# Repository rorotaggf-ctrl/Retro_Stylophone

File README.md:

# Retro Stylophone

A retro-style pocket synthesizer built with an ESP32 for **Hack Club Half-Life (Week 3: Design Your Instrument)**.

The instrument utilizes the ESP32's built-in capacitive touch peripheral to create a 13-pad chromatic keyboard directly out of exposed PCB copper pads, completely eliminating mechanical button wear and complex key soldering.

---

## Features

- **Microcontroller:** ESP32 NodeMCU (USB-C, dual-core 240 MHz, 320 KB SRAM)
- **Keyboard:** 13 capacitive touch PCB pads (Full chromatic octave: C4 to C5 including sharps/flats)
- **Sound Generation:** 5V Passive Piezo Buzzer driven via hardware PWM / DAC output
- **Modulation & Pitch-Bend:** 10K linear potentiometer for dynamic pitch modulation and glide effects
- **Octave / Mode Select:** SPDT mini slide switch for octave shifting and sound mode toggling
- **Form Factor:** Compact 2-layer PCB designed in KiCad with integrated GND planes

---

## Pinout Configuration

Everything is mounted using through-hole female pin headers so the ESP32 can be swapped or serviced at any time.

| Component | Pin Function | ESP32 Pin Header | Pin / GPIO | Notes |
| :--- | :--- | :--- | :--- | :--- |
| **Touch Keyboard** | C4 (Root) | `J2` Pin 13 | GPIO 4 | Capacitive Touch 0 |
| | C#4 | `J2` Pin 14 | GPIO 0 | Capacitive Touch 1 |
| | D4 | `J2` Pin 16 | GPIO 15 | Capacitive Touch 3 |
| | D#4 | `J2` Pin 15 | GPIO 2 | Capacitive Touch 2 |
| | E4 | `J1` Pin 15 | GPIO 13 | Capacitive Touch 4 |
| | F4 | `J1` Pin 13 | GPIO 12 | Capacitive Touch 5 |
| | F#4 | `J1` Pin 3 | GPIO 36 | High-impedance ADC antenna pad |
| | G4 | `J1` Pin 12 | GPIO 14 | Capacitive Touch 6 |
| | G#4 | `J1` Pin 4 | GPIO 39 | High-impedance ADC antenna pad |
| | A4 | `J1` Pin 11 | GPIO 27 | Capacitive Touch 7 |
| | A#4 | `J1` Pin 6 | GPIO 35 | High-impedance ADC antenna pad |
| | B4 (H4) | `J1` Pin 8 | GPIO 33 | Capacitive Touch 8 |
| | C5 (High C) | `J1` Pin 7 | GPIO 32 | Capacitive Touch 9 |
| **Audio Output** | Buzzer (+) | `J1` Pin 9 | GPIO 25 | Hardware PWM Audio Output |
| | Buzzer (-) | `J1` Pin 14 | GND | Common Ground |
| **Pitch Control** | Poti Wiper | `J1` Pin 5 | GPIO 34 | ADC1 Analog Input (0 - 3.3V) |
| | Poti Pin 1 / 3 | `J1` Pin 1 / 14 | 3V3 / GND | Potentiometer Reference Rails |
| **Octave Switch** | SW1 Center | `J2` Pin 8 | GPIO 19 | Active LOW (Internal Pull-Up) |
| | SW1 Pin 3 | `J1` Pin 14 | GND | Ground Reference Rail |

---

## Bill of Materials (BoM)

### Grant Funded Components (Tier 1 Limit: $30.00)

> [!NOTE]
> This parts list covers multipack items funded via Hack Club Half-Life. For the raw CSV file, see `BOM.csv`.

| Part | What it's for | Qty | Price (USD) | Price (EUR) | Vendor | Purchase Link |
| :--- | :--- | :--- | :--- | :--- | :--- | :--- |
| ESP32 NodeMCU USB-C (2-Pack) | Synthesizer sound engine & touch controller | 1 | $15.66 | 13,98 € | Amazon | [Amazon Link](https://www.amazon.de/dp/B0DB8CYQBS) |
| 10K Linear Potentiometer WH148 (10-Pack) | Pitch-bend and waveform modulation | 1 | $7.04 | 6,29 € | Amazon | [Amazon Link](https://www.amazon.de/dp/B0GVP99HZ2) |
| SPDT Mini Slide Switch (40-Pack) | Power and octave mode switch | 1 | $5.59 | 4,99 € | Amazon | [Amazon Link](https://www.amazon.de/dp/B07M9Z4CBP) |
| **Total** | | | **$28.29** | **25,26 €** | | |

*Remaining Tier 1 Budget: $1.71*

### Additional Self-Funded Components

> [!IMPORTANT]
> The following components are funded personally or sourced from existing workshop inventory to complete the build without exceeding the grant limit.

| Part | What it's for | Qty | Price (USD) | Price (EUR) | Vendor | Purchase Link |
| :--- | :--- | :--- | :--- | :--- | :--- | :--- |
| Custom 2-Layer PCB (5 copies) | Main stylophone PCB with capacitive touch pads | 1 | $8.10 | 7,23 € | JLCPCB | [JLCPCB Quote](https://jlcpcb.com/quote) |
| PCB Shipping (Standard Line) | Tracked delivery to Germany | 1 | $9.55 | 8,53 € | JLCPCB | [JLCPCB Quote](https://jlcpcb.com/quote) |
| Passive Piezo Buzzer 5V (20-Pack) | Acoustic square-wave chiptune audio output | 1 | $8.83 | 7,88 € | Amazon | [Amazon Link](https://www.amazon.de/dp/B0179I6LIK) |
| 100nF Ceramic Capacitors | Decoupling & noise filtering | 2 | $0.00 | 0,00 € | Inventory | Existing parts |
| Female Pin Headers 2.54mm | Removable socket for ESP32 | 2 | $0.00 | 0,00 € | Inventory | Existing parts |
| **Total Self-Funded** | | | **$26.48** | **23,64 €** | | |

---

## Software & Firmware

Developed in **VS Code** with PlatformIO and the Arduino framework.

- [ ] Hardware bench test (validating touch threshold tolerances, pot readings, and buzzer PWM)
- [ ] **Capacitive Touch Core:** Zero-bounce touch scanning for native touch pins (T0-T9) with adaptive baseline calibration
- [ ] **ADC Touch Matrix:** High-impedance antenna detection for remaining accidentals
- [ ] **Pitch-Bend & Glide:** Continuous frequency bend calculation via 10K potentiometer ADC readings
- [ ] **Octave Engine:** Real-time transposition (+12 semitones) via hardware slide switch
- [ ] **Chiptune Audio Driver:** Square-wave audio generation with low latency and distinct synth tone modes

---

## Hardware Previews & Design

### Initial Concept Sketch
Original top-down sketch outlining component placement, the 13-pad keyboard layout, potentiometer modulation, and buzzer position.

### KiCad Schematic
Full schematic featuring the 38-pin ESP32 socket headers, passive piezo buzzer, modulation potentiometer, slide switch, and 13 touch pad nets.

### PCB Layout
Completed 2-layer routing in KiCad with top and bottom ground copper pours and 0 DRC errors.

### 3D Render
Interactive 3D model view from KiCad showing the through-hole component headers, control pot, and exposed keyboard pads.

### Other

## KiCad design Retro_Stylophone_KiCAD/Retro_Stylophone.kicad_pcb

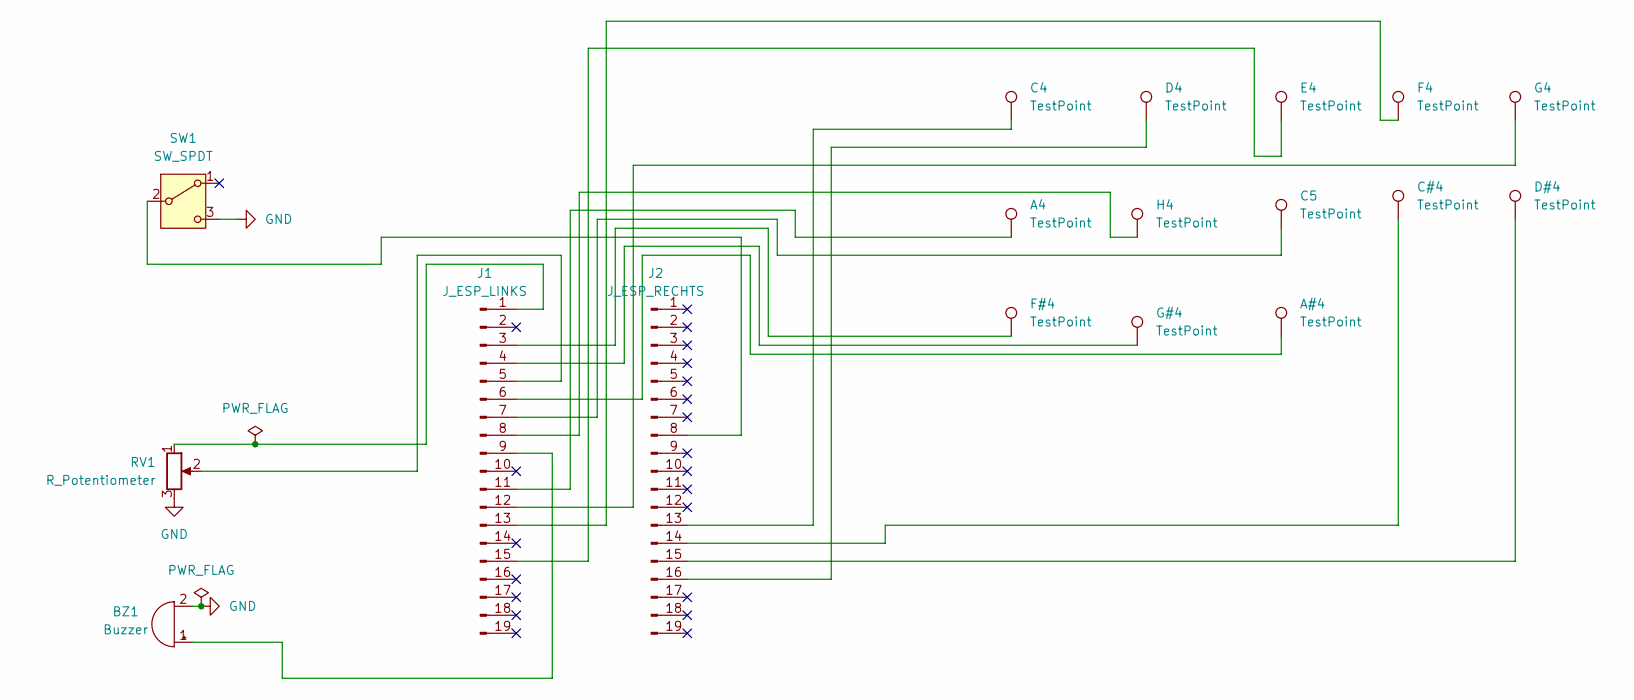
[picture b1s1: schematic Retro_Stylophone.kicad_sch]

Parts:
A4: TestPoint; TestPoint_Pad_D4.0mm
A#4: TestPoint; TestPoint_Pad_D4.0mm
BZ1: Buzzer; Buzzer_12x9.5RM7.6
C4, C5: TestPoint; TestPoint_Pad_D4.0mm
C#4: TestPoint; TestPoint_Pad_D4.0mm
D4: TestPoint; TestPoint_Pad_D4.0mm
D#4: TestPoint; TestPoint_Pad_D4.0mm
E4: TestPoint; TestPoint_Pad_D4.0mm
F4: TestPoint; TestPoint_Pad_D4.0mm
F#4: TestPoint; TestPoint_Pad_D4.0mm
G4: TestPoint; TestPoint_Pad_D4.0mm
G#4: TestPoint; TestPoint_Pad_D4.0mm
H4: TestPoint; TestPoint_Pad_D4.0mm
J1: J_ESP_LINKS; PinSocket_1x19_P2.54mm_Vertical
J2: J_ESP_RECHTS; PinSocket_1x19_P2.54mm_Vertical
RV1: R_Potentiometer; Potentiometer_Alps_RK09L_Single_Vertical
SW1: SW_SPDT; SW_Slide_SPDT_Angled_CK_OS102011MA1Q

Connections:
GND: BZ1.2 (-), RV1.3, SW1.3 (C)
unnamed: BZ1.1 (+), J1.9
unnamed: J1.1, RV1.1
unnamed: F#4.1 (1_1), J1.3
unnamed: G#4.1 (1_1), J1.4
unnamed: J1.5, RV1.2
unnamed: A#4.1 (1_1), J1.6
unnamed: C5.1 (1_1), J1.7
unnamed: H4.1 (1_1), J1.8
unnamed: A4.1 (1_1), J1.11
unnamed: G4.1 (1_1), J1.12
unnamed: F4.1 (1_1), J1.13
unnamed: E4.1 (1_1), J1.15
unnamed: J2.8, SW1.2 (B)
unnamed: C4.1 (1_1), J2.13
unnamed: C#4.1 (1_1), J2.14
unnamed: D#4.1 (1_1), J2.15
unnamed: D4.1 (1_1), J2.16

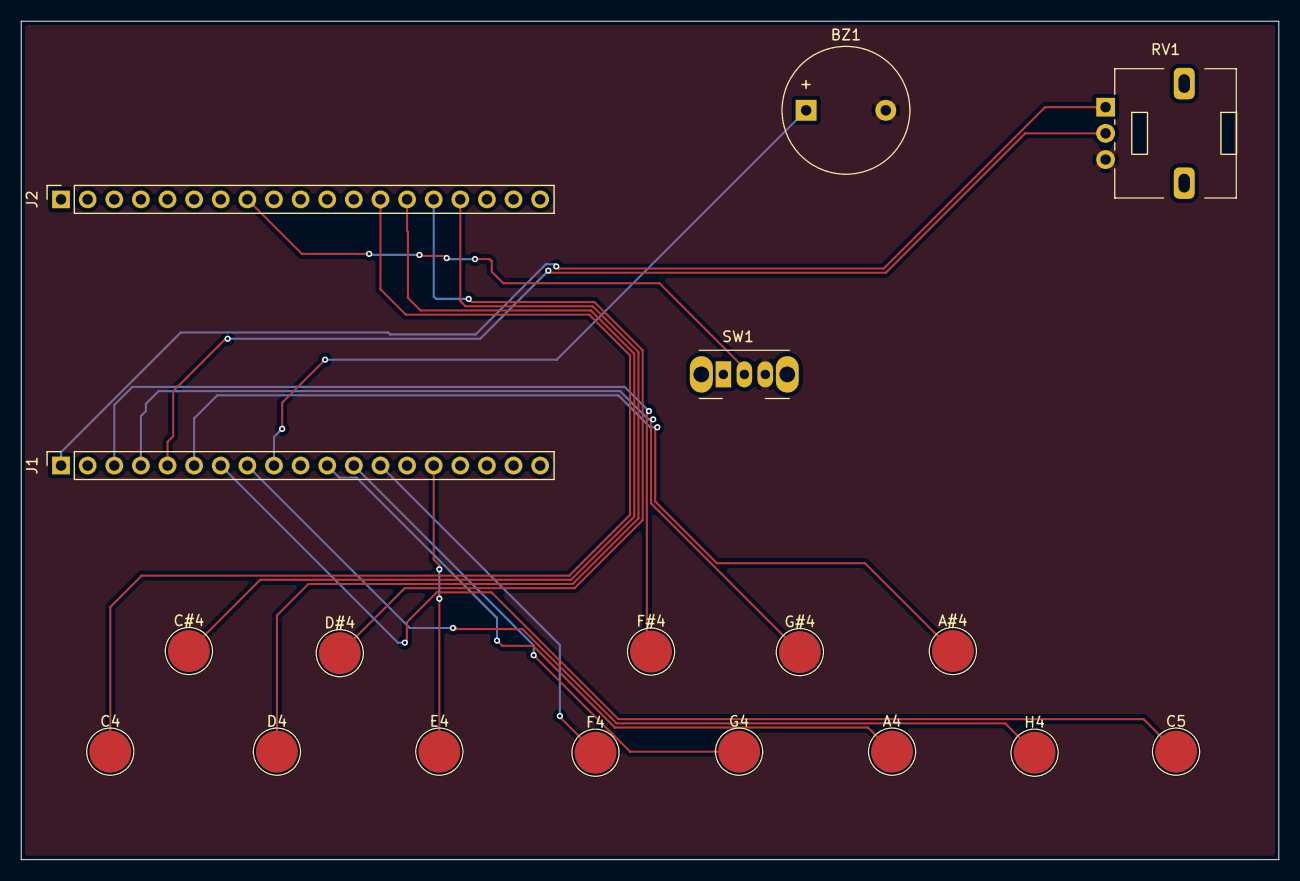
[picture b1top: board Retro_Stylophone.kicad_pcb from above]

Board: 2 copper layers, 120.0 x 80.0 mm, 18 parts (0 on the bottom side), 18 nets.
